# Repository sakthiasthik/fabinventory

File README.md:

# FabInventory

**Git-backed inventory & BOM management for hardware engineers.**

FabInventory helps hardware teams manage project BOMs, aggregate master inventory, track stock levels, and create purchase orders — all backed by Git for version control and collaboration. No cloud, no database server — just clone and run.

---

## Features

| | |
|---|---|
| 📋 **Multi-project BOMs** | Upload CSV/Excel BOMs for electrical, mechanical, PCB, and 3D-print projects |
| 🔄 **Auto aggregation** | Master inventory auto-calculated from all project BOMs — always consistent |
| 📦 **Stock tracking** | Track current stock per component with auto-calculated "to order" quantities |
| 📊 **Tabled inventory** | Four tabs — Electrical · Mechanical · PCB · 3D Print |
| 📥 **Bulk stock import** | Upload existing stock lists via Excel/CSV |
| 🛒 **Purchase orders** | Create orders, track status (draft → ordered → shipped → received) |
| 🔀 **Git integration** | Auto-commits on every change, push/pull via UI, full commit history |
| 👤 **Git identity** | Commits are attributed to each user's real Git identity — you know who changed what |
| 🔐 **Authentication** | Password login + optional GitHub OAuth |
| 🖥️ **Cross-platform** | Runs on Linux, macOS, and Windows |

---

## Quick Start

```bash
git clone https://github.com/sakthiasthik/fabinventory.git
cd fabinventory
python run.py
```

That's it. The app auto-creates `.env` on first run, installs any missing dependencies, and starts at **http://localhost:9000**.

Login with the default password: **`fabinventory`** (change it in `.env` after first login).

> **Requirements:** Python 3.8+, Git (optional but recommended)

---

## Installation (detailed)

### Prerequisites
- Python 3.8 or higher
- Git (optional — for version control features)

### Option 1: Run directly (recommended)
```bash
git clone https://github.com/sakthiasthik/fabinventory.git
cd fabinventory
python run.py
```
`run.py` auto-installs missing packages and starts the server.

### Option 2: pip install
```bash
git clone https://github.com/sakthiasthik/fabinventory.git
cd fabinventory
pip install -e .
fabinventory
```

### Option 3: Virtual environment
```bash
git clone https://github.com/sakthiasthik/fabinventory.git
cd fabinventory
python3 -m venv venv
source venv/bin/activate        # Linux/macOS
# venv\Scripts\activate         # Windows
pip install -r requirements.txt
python run.py
```

---

## First Run Setup

1. Open **http://localhost:9000**
2. Log in with password **`fabinventory`**
3. On the setup page, enter your **2-letter company prefix** (e.g., `SA` for "Sakthi")
4. This prefix is used for internal part numbers: `SA-ELE-00001`, `SA-MEC-00001`, etc.

---

## Usage

### 1. Create a Project
- Go to **Projects** → **Create Project**
- Give it a name and optional BOM file
- Projects can have: Electrical, Mechanical, PCB, and 3D Print BOMs

### 2. Upload BOMs
- Open a project → choose the tab (Electrical / Mechanical / PCB / 3D Print)
- Upload CSV or Excel BOM files
- Master inventory auto-updates across all projects

### 3. Track Stock
- Go to **Inventory** → view aggregated components across all projects
- Click the ✏️ icon to update stock for any component
- Use **Import Stock** to bulk-upload existing stock from Excel

### 4. Create Orders
- Go to **Orders** → **Create Order**
- Select projects and components to order
- Track order status: draft → ordered → shipped → received
- When received, stock levels auto-update

### 5. Git Sync
- Every data change is auto-committed locally
- Use the **navbar sync widget** to commit and push
- Set up a remote in **Git Settings** — works with GitHub, GitLab, Bitbucket (SSH or HTTPS)
- The widget shows how many commits are pending push

---

## Project Structure

```
fabinventory/
├── run.py                    # Entry point (auto-installs deps)
├── requirements.txt          # Python dependencies
├── setup.py                  # pip-installable package
├── .env.example              # Environment template
├── src/
│   ├── app.py                # Flask setup, auth, state, blueprint registration
│   ├── models.py             # Data models (dataclasses)
│   ├── file_manager.py       # JSON file read/write
│   ├── project_manager.py    # Project CRUD
│   ├── inventory_manager.py  # Inventory & order logic
│   ├── aggregator.py         # BOM → master inventory aggregation
│   ├── bom_parser.py         # CSV/XLSX BOM parser
│   ├── git_manager.py        # Git commit/push/pull
│   └── routes/               # Flask Blueprints (route organisation)
│       ├── main.py           # Auth + core pages (/login, /setup, /dashboard...)
│       ├── projects.py       # Project routes (/project/*)
│       ├── inventory.py      # Inventory routes (/inventory/*)
│       ├── orders.py         # Order routes (/order/*)
│       ├── api.py            # REST API endpoints (/api/*)
│       └── git_routes.py     # Git settings (/git-settings)
├── templates/                # Jinja2 HTML templates
├── static/                   # CSS, JS, BOM template
├── fabinventory_data/        # Your data (auto-created)
│   ├── config.json
│   ├── master/               # Aggregated inventories
│   ├── projects/             # Per-project BOMs & files
│   └── orders/               # Purchase orders
└── test/                     # Pytest test suite
```

### Blueprint architecture

Routes are split by domain so each file is small and easy to find:

| Blueprint | File | URL prefix | What lives there |
|---|---|---|---|
| `main` | `routes/main.py` | _(none)_ | Login, logout, setup, dashboard, project listing |
| `project` | `routes/projects.py` | `/project` | Project detail, BOM uploads, images, Gerber, delete |
| `inventory` | `routes/inventory.py` | `/inventory` | Master inventory view, stock update, import |
| `orders` | `routes/orders.py` | _(none)_ | Order list, create, receive, summary |
| `api` | `routes/api.py` | `/api` | JSON REST endpoints |
| `git` | `routes/git_routes.py` | _(none)_ | Git settings, commit, push, pull |

---

## Data Storage

All data is stored as **human-readable JSON files** in `fabinventory_data/`. No database required.

| File | Contents |
|---|---|
| `master/electronics.json` | Aggregated electrical components |
| `master/mechanical.json` | Aggregated mechanical parts |
| `master/pcb.json` | Aggregated PCB boards |
| `master/print3d.json` | Aggregated 3D print parts |
| `projects/<name>/bom.json` | Project electrical BOM |
| `projects/<name>/meta.json` | Project metadata |
| `orders/PO-*.json` | Purchase orders |

The `DATA_PATH` in `.env` controls where this folder lives. Set it to an absolute path to keep data separate from code.

---

## BOM File Format

### Electrical BOM columns
| Column | Description |
|---|---|
| `SI.No` | Serial number |
| `Reference` | Designator (R1, C2, U1…) |
| `Value` | Component value (10k, 100nF…) |
| `Footprint` | Package (0603, SOT-23…) |
| `Manufacturer_Part_Number` | MPN |
| `Manufacturer_Name` | Manufacturer |
| `Qty` | Quantity per board |
| `DNP` | Do Not Populate (X/Yes/1 = skip) |

Download the template from the app: **Projects → any project → Download template**

### Aggregation key
Components are deduplicated by **value + footprint**. Two projects using `100nF 0603` get merged into one master inventory item with combined quantity.

---

## Environment Variables

| Variable | Default | Description |
|---|---|---|
| `SECRET_KEY` | auto-generated | Flask session encryption key |
| `DATA_PATH` | `./fabinventory_data` | Where data JSON files are stored |
| `ADMIN_PASSWORD` | `fabinventory` | Login password |
| `GITHUB_CLIENT_ID` | _(empty)_ | Enable GitHub OAuth login |
| `GITHUB_CLIENT_SECRET` | _(empty)_ | Enable GitHub OAuth login |

The `.env` file is **auto-created on first run** — you don't need to copy `.env.example` manually.

---

## Git Workflow

FabInventory uses a **single-repo** architecture — the project repo itself is the version-controlled source of truth.

- **Auto-commit**: Every project change, BOM upload, stock update, and order creation is auto-committed
- **Push/Pull**: Use the navbar widget or Git Settings page to sync with a remote
- **Identity**: Commits use your real Git `user.name` / `user.email` from the repo config
- **Unpushed tracking**: The navbar shows exactly how many commits are pending push

For team use: set up a shared remote (GitHub/GitLab/Bitbucket) in Git Settings, and each member pushes/pulls to stay in sync.

---

## Standalone Executable (all platforms)

Build a single-folder executable that runs without Python or pip:

```bash
pip install pyinstaller
pyinstaller fabinventory.spec --noconfirm
```

Output: `dist/FabInventory/` — zip this folder and distribute.

| File | Purpose |
|---|---|
| `dist/FabInventory/FabInventory` | Double-click to launch (or `./FabInventory` in terminal) |
| `dist/FabInventory/_internal/` | Bundled Python + dependencies (don't touch) |

The app auto-creates `.env` and `fabinventory_data/` on first run. Browser opens at `http://localhost:9000`.

> **Note:** Do NOT commit `dist/` or `build/` to Git — they are build artifacts. They are already in `.gitignore`. Only commit `fabinventory.spec` (the build recipe).

---

## Development

```bash
# Run tests
pip install pytest
python -m pytest test/ -v

# Run the app in debug mode
python run.py
# → http://localhost:9000 (debug mode auto-reloads on code changes)

# Build executable
pip install pyinstaller
pyinstaller fabinventory.spec --noconfirm
```

---

## License

MIT License — see [LICENSE](LICENSE)

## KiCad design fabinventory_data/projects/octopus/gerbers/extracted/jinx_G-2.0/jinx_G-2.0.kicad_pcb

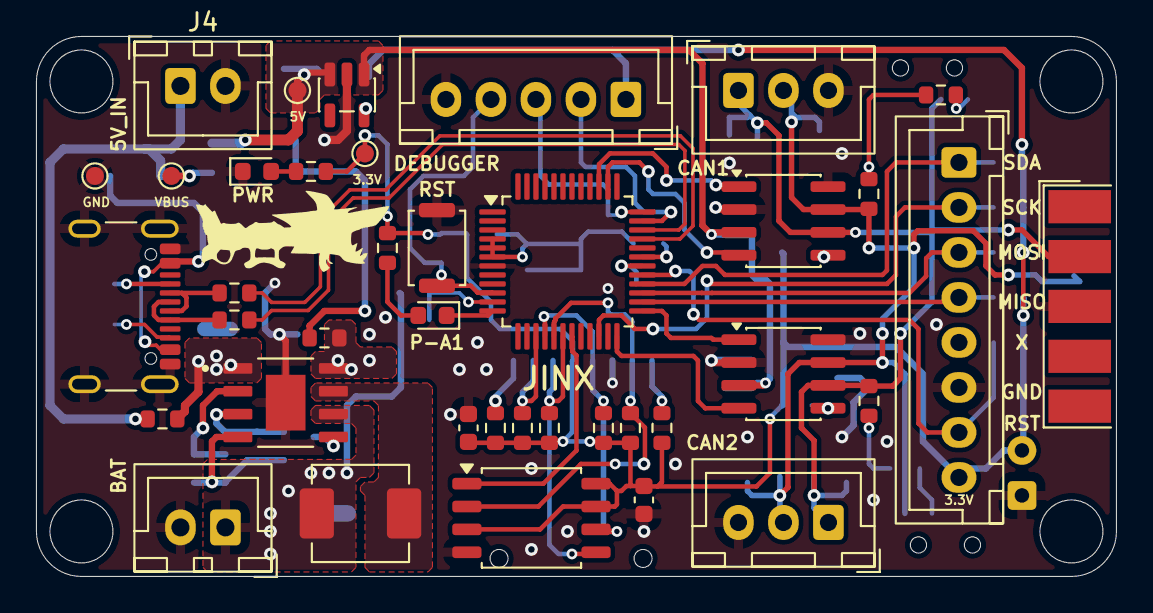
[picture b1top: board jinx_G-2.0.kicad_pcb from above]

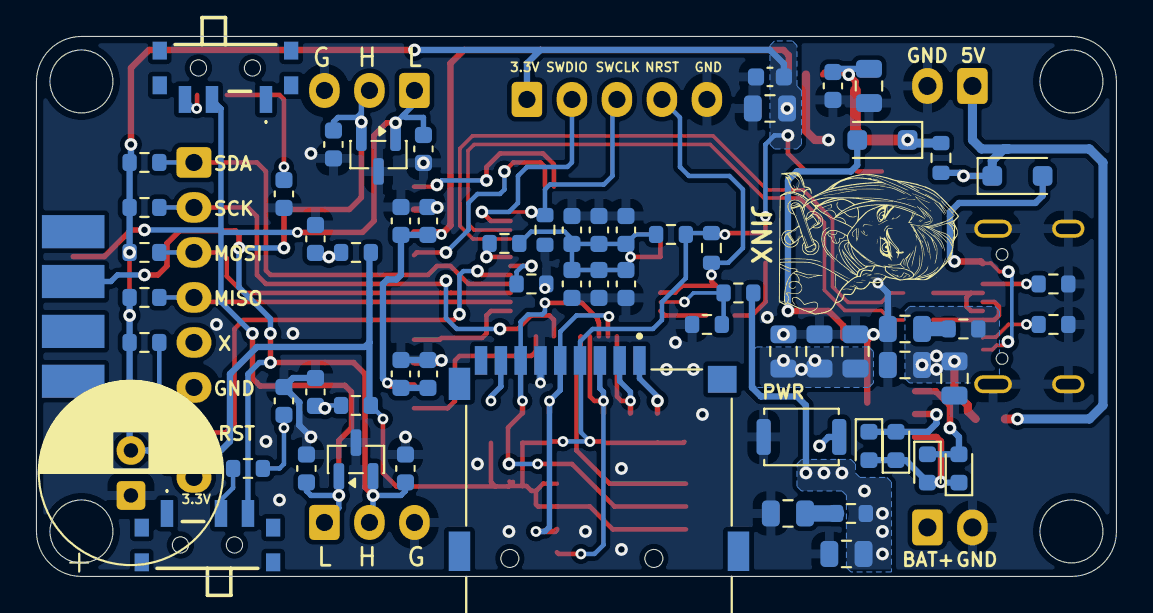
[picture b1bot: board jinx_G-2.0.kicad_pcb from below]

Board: 2 copper layers, 60.0 x 30.0 mm, 102 parts (63 on the bottom side), 56 nets.

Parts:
3.3V1: 3.3V; TestPoint_Pad_D1.0mm
5V1: 5V; TestPoint_Pad_D1.0mm
C1, C2, C3, C4, C5, C6, C12, C14, C20, C21, C22, C23, C32, C33: 100nF; C_0603_1608Metric
C7: 100uF; CP_Radial_D10.0mm_P2.50mm
C8, C9, C11, C16, C18: 10uF; C_0805_2012Metric
C10, C13: 4.7uF; C_0805_2012Metric
C15, C17, C19: 22uF; C_0805_2012Metric
C24, C25: 1uF; C_0603_1608Metric
C26, C27, C28, C29: 47pF; C_0603_1608Metric
C30, C31: 4.7nF; C_0603_1608Metric
D1, D3: LED_BLUE; LED_0603_1608Metric
D2, D10: DSK34; D_SOD-123F
D4: LED_Blue; LED_0603_1608Metric
D5, D6, D7: LED_RED; LED_0603_1608Metric
D8, D9: NUP2105L; SOT-23
GND1: GND; TestPoint_Pad_D1.0mm
J1: USB_C_Receptacle_USB2.0_14P; USB_C_Receptacle_GCT_USB4105-xx-A_16P_TopMnt_Horizontal
J2: Conn_01x05_Pin; JST_XH_B5B-XH-A_1x05_P2.50mm_Vertical
J3: Conn_01x08_Pin; JST_XH_B8B-XH-A_1x08_P2.50mm_Vertical
J4, J5: Conn_01x02_Pin; JST_XH_B2B-XH-A_1x02_P2.50mm_Vertical
J6: DE9_Socket; DSUB-9_Socket_EdgeMount_P2.77mm
J7: CAN1; JST_XH_B3B-XH-A_1x03_P2.50mm_Vertical
J8: CAN2; JST_XH_B3B-XH-A_1x03_P2.50mm_Vertical
J9: Micro_SD_Card; CUI_MSD-4-A
L1: 1uH; L_Vishay_IHLP-2020
PWR1: SW_Push; SW_Push_SPST_NO_Alps_SKRK
R1, R6, R7, R15, R19, R20, R21, R29, R31, R33, R34, R35: 0R; R_0603_1608Metric
R2, R3, R11, R12, R13, R14, R26, R27, R28, R30, R32: 10kR; R_0603_1608Metric
R4, R18: 1K; R_0603_1608Metric
R5, R8: 5.11kR; R_0603_1608Metric
R9, R10: 100K; R_0603_1608Metric
R16, R17: 2R; R_0603_1608Metric
R22: 60.4; R_0603_1608Metric
R23, R24, R25: 60.4R; R_0603_1608Metric
RST1: SW_Push; SW_Push_SPST_NO_Alps_SKRK
S1, S2: PCM12SMTBR
U1: STM32G0B1CBTx; LQFP-48_7x7mm_P0.5mm
U2: TLV75733PDBV; SOT-23-5
U3: IP5306; SOP127P600X165-9N
U4, U5: TJA1042T-3; SOIC-8_3.9x4.9mm_P1.27mm
U6: W25Q32JVSS; SOIC-8_5.3x5.3mm_P1.27mm
VBUS1: 5V; TestPoint_Pad_D1.0mm

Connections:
+3.3V: 3.3V1.1, C7.2, C13.1, C14.1, C32.1, C33.1, J2.1, J3.8, J9.4 (VDD), R1.1, R2.1, R4.2, R11.1, R12.2, R13.1, R14.1, R18.2, R20.1, R21.1, R26.1, R27.1, R28.1, R29.1, R30.1, R31.1, R32.2, U2.5 (OUT), U6.3 (~WP/IO_{2}), U6.7 (~HOLD/~RESET/IO_{3}), U6.8 (VCC)
+5V: 5V1.1, C10.1, C12.1, C22.2, C23.2, C24.2, C25.2, D10.1 (K), R33.2, U2.1 (IN), U2.3 (EN), U4.3 (VCC), U5.3 (VCC)
/COMMUNICATION/CAN1_H: C26.1, C28.1, D8.2 (K), D9.2 (K), J6.7, J7.2, J8.2, R22.2, S1.3 (NO), U4.7 (CANH), U5.7 (CANH)
/COMMUNICATION/CAN1_L: C27.1, C29.1, D8.1 (K), D9.1 (K), J6.2, J7.1, J8.1, R25.1, S2.2 (COM), U4.6 (CANL), U5.6 (CANL)
/COMMUNICATION/CAN1_RX: U1.38 (PD0), U4.4 (RXD)
/COMMUNICATION/CAN1_TX: U1.39 (PD1), U4.1 (TXD)
/COMMUNICATION/CAN2_RX: U1.24 (PB12), U5.4 (RXD)
/COMMUNICATION/CAN2_TX: U1.25 (PB13), U5.1 (TXD)
/DC_DC/BAT+: C16.1, J5.1, L1.2, R10.2, R17.2, U3.6 (BAT)
/MCU/D+: J1.A6 (D+), J1.B6 (D+), R7.1
/MCU/D-: J1.A7 (D-), J1.B7 (D-), R6.1
/MCU/FLASH_CS: U1.19 (PB0), U6.1 (~CS)
/MCU/LED_PIN: D1.1 (K), U1.12 (PA1)
/MCU/M3.3V: C1.1, C2.1, C3.1, C4.2, C5.1, C6.2, R1.2, R35.1, U1.4 (VBAT), U1.5 (VREF+), U1.6 (VDD)
/MCU/M_N: R6.2, U1.33 (PA9/PA11)
/MCU/M_NRST: J2.4, R2.2, RST1.2, U1.10 (PF2)
/MCU/M_P: R7.2, U1.34 (PA10/PA12)
/MCU/M_SWCLK: J2.3, R3.2, U1.36 (PA14)
/MCU/M_SWDIO: J2.2, U1.35 (PA13)
/MCU/SD_CS: J9.2 (DAT3/CD), R26.2, U1.15 (PA4)
/MCU/SPI2_MISO: J3.4, R14.2, U1.26 (PB14)
/MCU/SPI2_MOSI: J3.3, R13.2, U1.27 (PB15)
/MCU/SPI2_RST: J3.7, R12.1, U1.29 (PA9/UCPD1_DBCC1)
/MCU/SPI2_SCK: J3.2, R11.2, U1.22 (PB10)
/MCU/SPI2_SDA: J3.1, R32.1, U1.28 (PA8)
/SPI_FLASH/SPI_CLK: J9.5 (CLK), R27.2, U1.16 (PA5), U6.6 (CLK)
/SPI_FLASH/SPI_MISO: J9.7 (DAT0), R30.2, U1.17 (PA6), U6.2 (DO/IO_{1})
/SPI_FLASH/SPI_MOSI: J9.3 (CMD), R28.2, U1.18 (PA7), U6.5 (DI/IO_{0})
GND: C1.2, C2.2, C3.2, C4.1, C5.2, C6.1, C7.1, C8.1, C9.2, C10.2, C11.2, C12.2, C13.2, C14.2, C15.2, C16.2, C17.2, C18.1, C19.2, C20.2, C21.2, C22.1, C23.1, C24.1, C25.1, C26.2, C27.2, C28.2, C29.2, C30.2, C31.2, C32.2, C33.2, D4.1 (K), D8.3 (A), D9.3 (A), GND1.1, J1.A1 (GND), J1.A12 (GND), J1.B1 (GND), J1.B12 (GND), J1.S1 (SHIELD), J2.5, J3.6, J4.2, J5.2, J6.3, J7.3, J8.3, J9.6 (VSS), PWR1.1, R3.1, R5.2, R8.2, R9.2, R34.1, RST1.1, U1.7 (VSS), U2.2 (GND), U3.9 (POWERPAD), U4.2 (GND), U4.8 (STB), U5.2 (GND), U5.8 (STB), U6.4 (GND)
unnamed: C8.2, R16.1
unnamed: C18.2, R17.1
unnamed: C30.1, R22.1, R23.2
unnamed: C31.1, R24.1, R25.2
unnamed: D1.2 (A), R4.1
unnamed: D2.2 (A), J1.A4 (VBUS), J1.A9 (VBUS), J1.B4 (VBUS), J1.B9 (VBUS)
unnamed: D3.2 (A), D5.1 (K), D6.2 (A), D7.1 (K), U3.4 (LED3)
unnamed: D3.1 (K), D5.2 (A), U3.3 (LED2)
unnamed: D4.2 (A), R18.1
unnamed: D6.1 (K), D7.2 (A), U3.2 (LED1)
unnamed: D10.2 (A), R19.2
unnamed: J1.A5 (CC1), R5.1
unnamed: J1.B5 (CC2), R8.1
unnamed: J9.8 (DAT1), R31.2
unnamed: J9.1 (DAT2), R29.2
unnamed: R24.2, S1.2 (COM)
unnamed: R23.1, S2.3 (NO)
unnamed: R9.1, R10.1, U1.11 (PA0)
unnamed: R34.2, U1.30 (PC6)
unnamed: R35.2, U1.31 (PC7)
unnamed: PWR1.2, U3.5 (KEY)
unnamed: L1.1, U3.7 (SW)
unnamed: C9.1, C11.1, R15.2, R16.2, U3.1 (VIN)
unnamed: C15.1, C17.1, C19.1, R19.1, U3.8 (VOUT)
unnamed: C20.1, R20.2, U4.5 (VIO)
unnamed: C21.1, R21.2, U5.5 (VIO)
VBUS: D2.1 (K), J4.1, R15.1, R33.1, VBUS1.1

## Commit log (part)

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2026-03-01 FabInventory Readme added
2026-03-02 files creadted
2026-03-02 Auto update config prefix
2026-04-27 test changes in the project html file
2026-04-27 Fixed BOM upload/parsing, added template download, resolved order serialization, and improved dashboard navigation
2026-04-28 Working Basic Code
2026-04-30 chore: rename requirement.txt to requirements.txt
2026-04-30 chore: move all files from FAB_INVENTORY to project root
2026-04-30 chore: add LICENSE, .env.example, update README with setup instructions, and adjust gitignore
2026-04-30 ux: improve information hierarchy, sync visibility, and reduce noise
2026-05-11 Created Login pAge based on GIt Hub order page Qunatity can be edit while order
2026-06-25 kashish changes & wip for order page
2026-06-26 Updated order page
2026-06-27 Secret Key Bug fixed
2026-06-27 bug 2 Fixed
2026-06-27 2 more bug fixed Like CSRF Protect & other one
2026-06-27 2 nore Bug fixed with CSRF Protection
2026-06-27 Total 16 bug fixed so far
2026-06-27 All old Data Deleted for the testing
2026-06-27 Every thing is cleared & before Teseting From scracth
2026-06-30 updated orders, project and inventory page
2026-06-30 Mid Of testing
